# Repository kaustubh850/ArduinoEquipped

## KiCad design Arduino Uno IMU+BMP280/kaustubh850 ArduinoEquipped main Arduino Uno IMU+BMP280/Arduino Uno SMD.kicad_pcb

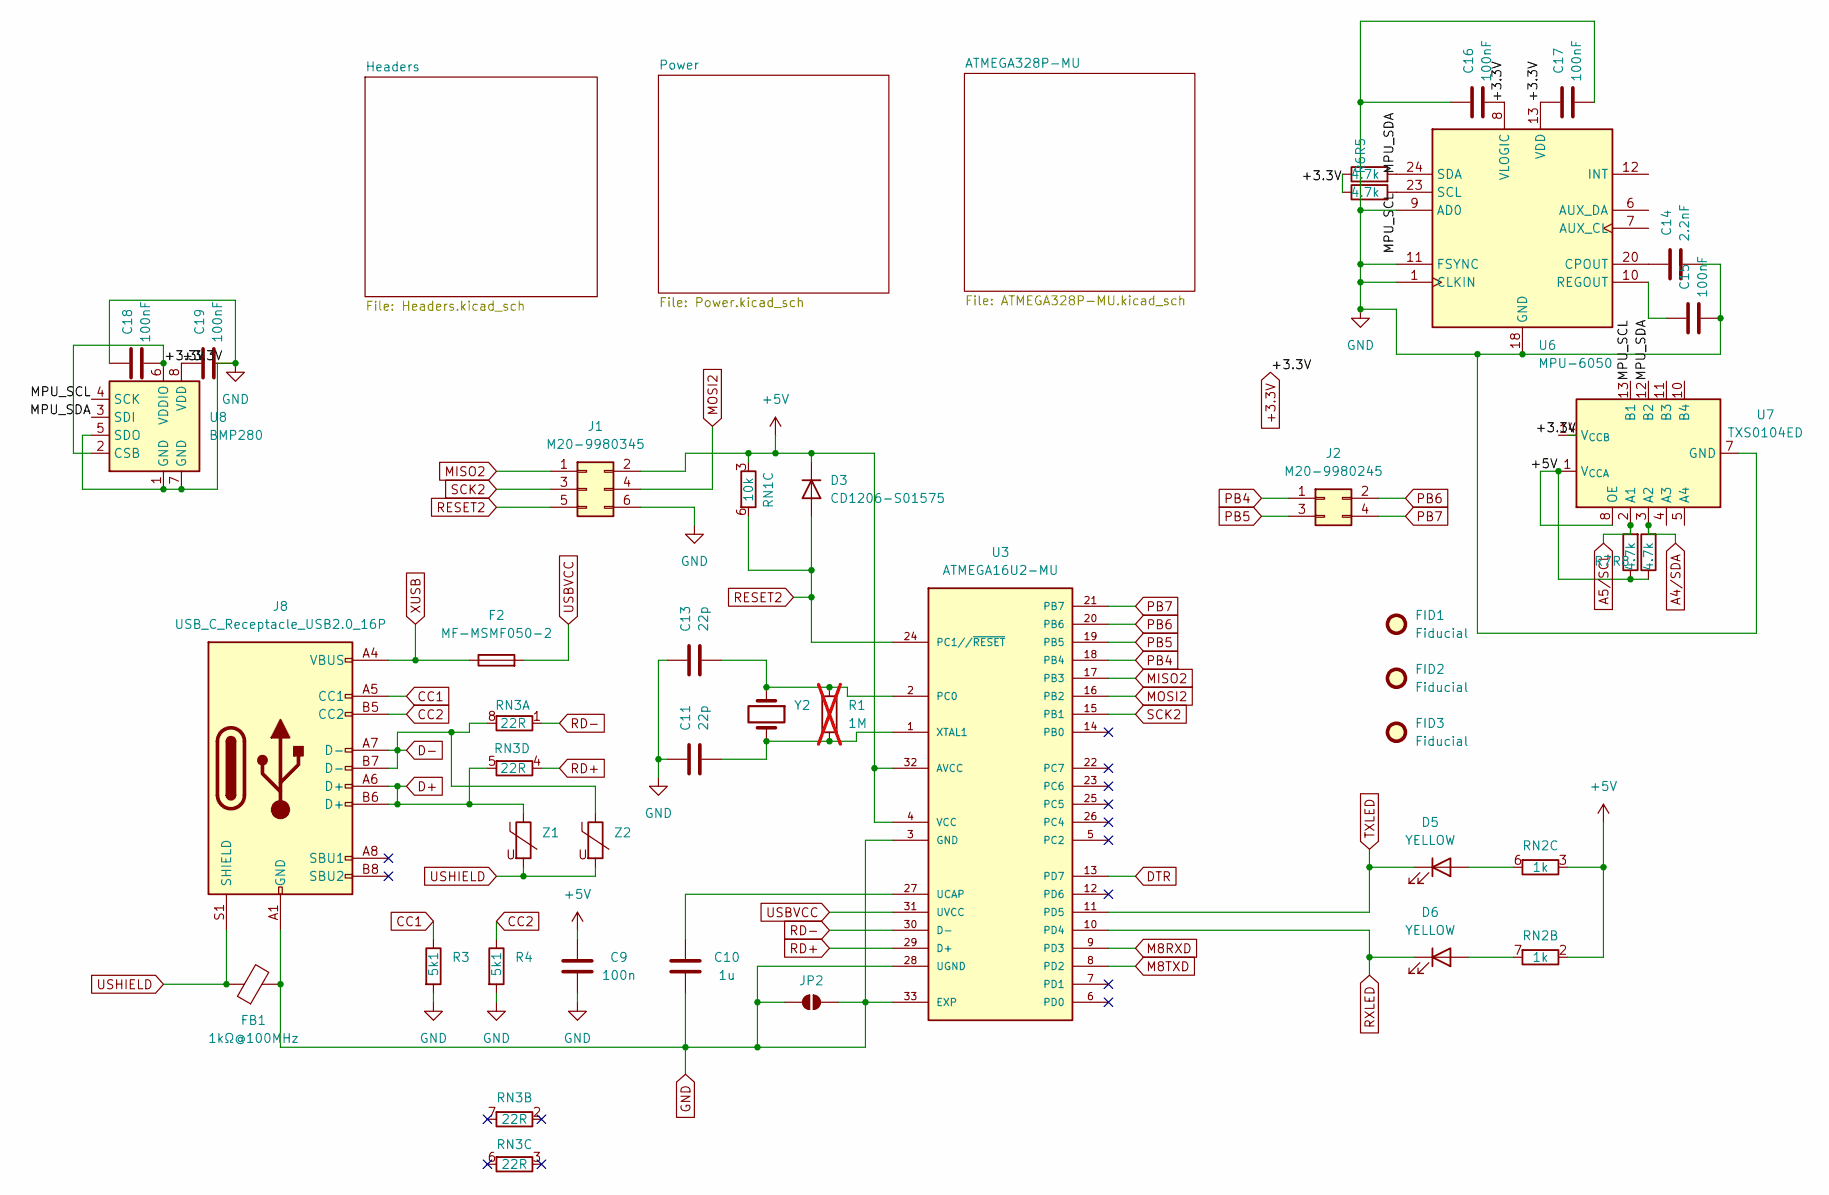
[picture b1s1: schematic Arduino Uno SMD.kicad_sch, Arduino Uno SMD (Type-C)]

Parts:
C9: 100n; C_0603_1608Metric
C10: 1u; C_0603_1608Metric
C11, C13: 22p; C_0603_1608Metric
C14: 2.2nF; C_0603_1608Metric
C15, C16, C17, C18, C19: 100nF; C_0603_1608Metric
D3: CD1206-S01575; D_1206_3216Metric
D5, D6: YELLOW; LED_0805_2012Metric
F2: MF-MSMF050-2; Fuse_1812_4532Metric_Pad1.30x3.40mm_HandSolder
FB1: 1kΩ@100MHz; L_0805_2012Metric
FID1, FID2, FID3: Fiducial; Fiducial_1mm_Mask2mm
J1: M20-9980345; PinHeader_2x03_P2.54mm_Vertical
J2: M20-9980245; CONN_M20-9980245_HRW
J8: USB_C_Receptacle_USB2.0_16P; USB_C_Receptacle_GCT_USB4105-xx-A_16P_TopMnt_Horizontal
JP2: SolderJumper_2_Open; SolderJumper-2_P1.3mm_Open_Pad1.0x1.5mm
R1: 1M; R_0603_1608Metric; not fitted
R3, R4: 5k1; R_0603_1608Metric
R5, R6, R7, R8: 4.7k; R_0603_1608Metric
RN1: 10k; R_Array_Convex_4x0603
RN2: 1k; R_Array_Convex_4x0603
RN3: 22R; R_Array_Convex_4x0603
U3: ATMEGA16U2-MU; VQFN-32-1EP_5x5mm_P0.5mm_EP3.1x3.1mm
U6: MPU-6050; InvenSense_QFN-24_4x4mm_P0.5mm
U7: TXS0104ED; SOIC-14_3.9x8.7mm_P1.27mm
U8: BMP280; Bosch_LGA-8_2x2.5mm_P0.65mm_ClockwisePinNumbering
Y2: LFXTAL003240BULK; Crystal_HC49-4H_Vertical
Z1, Z2: 5pF@1MHz; R_0603_1608Metric

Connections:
+3.3V: C16.1, C17.2, C18.1, C19.2, R5.1, R6.1, U6.8 (VLOGIC), U6.13 (VDD), U8.2 (CSB), U8.6 (VDDIO), U8.8 (VDD); also elsewhere on the board
+5V: C9.1, D3.1 (K), J1.2, R7.1, R8.1, RN1.3 (R3.1), RN2.2 (R2.1), RN2.3 (R3.1), U3.4 (VCC), U3.32 (AVCC), U7.1 (V_{CCA}), U7.8 (OE); also elsewhere on the board
/MPU_SCL: R6.2, U6.23 (SCL), U7.13 (B1), U8.4 (SCK)
/MPU_SDA: R5.2, U6.24 (SDA), U7.12 (B2), U8.3 (SDI)
A4/SDA: R8.2, U7.3 (A2); also elsewhere on the board
A5/SCL: R7.2, U7.2 (A1); also elsewhere on the board
CC1: J8.A5 (CC1), R3.1
CC2: J8.B5 (CC2), R4.1
D+: J8.A6 (D+), J8.B6 (D+), RN3.5 (R4.2), Z1.1
D-: J8.A7 (D-), J8.B7 (D-), RN3.8 (R1.2), Z2.1
DTR: U3.13 (PD7); also elsewhere on the board
GND: C9.2, C10.1, C11.2, C13.2, C14.1, C15.1, C16.2, C17.1, C18.2, C19.1, FB1.2, J1.6, J8.A1 (GND), J8.A12 (GND), J8.B1 (GND), J8.B12 (GND), JP2.1 (A), JP2.2 (B), R3.2, R4.2, U3.3 (GND), U3.28 (UGND), U3.33 (EXP), U6.1 (CLKIN), U6.9 (AD0), U6.11 (FSYNC), U6.18 (GND), U7.7 (GND), U8.1 (GND), U8.5 (SDO), U8.7 (GND); also elsewhere on the board
M8RXD: U3.9 (PD3); also elsewhere on the board
M8TXD: U3.8 (PD2); also elsewhere on the board
MISO2: J1.1, U3.17 (PB3)
MOSI2: J1.4, U3.16 (PB2)
unnamed: D5.2 (A), RN2.6 (R3.2)
unnamed: D6.2 (A), RN2.7 (R2.2)
unnamed: C13.1, R1.1, U3.2 (PC0), Y2.1
unnamed: C10.2, U3.27 (UCAP)
unnamed: C11.1, R1.2, U3.1 (XTAL1), Y2.2
unnamed: C14.2, U6.20 (CPOUT)
unnamed: C15.2, U6.10 (REGOUT)
PB4: J2.1, U3.18 (PB4)
PB5: J2.3, U3.19 (PB5)
PB6: J2.2, U3.20 (PB6)
PB7: J2.4, U3.21 (PB7)
RD+: RN3.4 (R4.1), U3.29 (D+)
RD-: RN3.1 (R1.1), U3.30 (D-)
RESET2: D3.2 (A), J1.5, RN1.6 (R3.2), U3.24 (PC1//~RESET)
RXLED: D6.1 (K), U3.10 (PD4)
SCK2: J1.3, U3.15 (PB1)
TXLED: D5.1 (K), U3.11 (PD5)
USBVCC: F2.2, U3.31 (UVCC); also elsewhere on the board
USHIELD: FB1.1, J8.S1 (SHIELD), Z1.2, Z2.2
XUSB: F2.1, J8.A4 (VBUS), J8.A9 (VBUS), J8.B4 (VBUS), J8.B9 (VBUS)

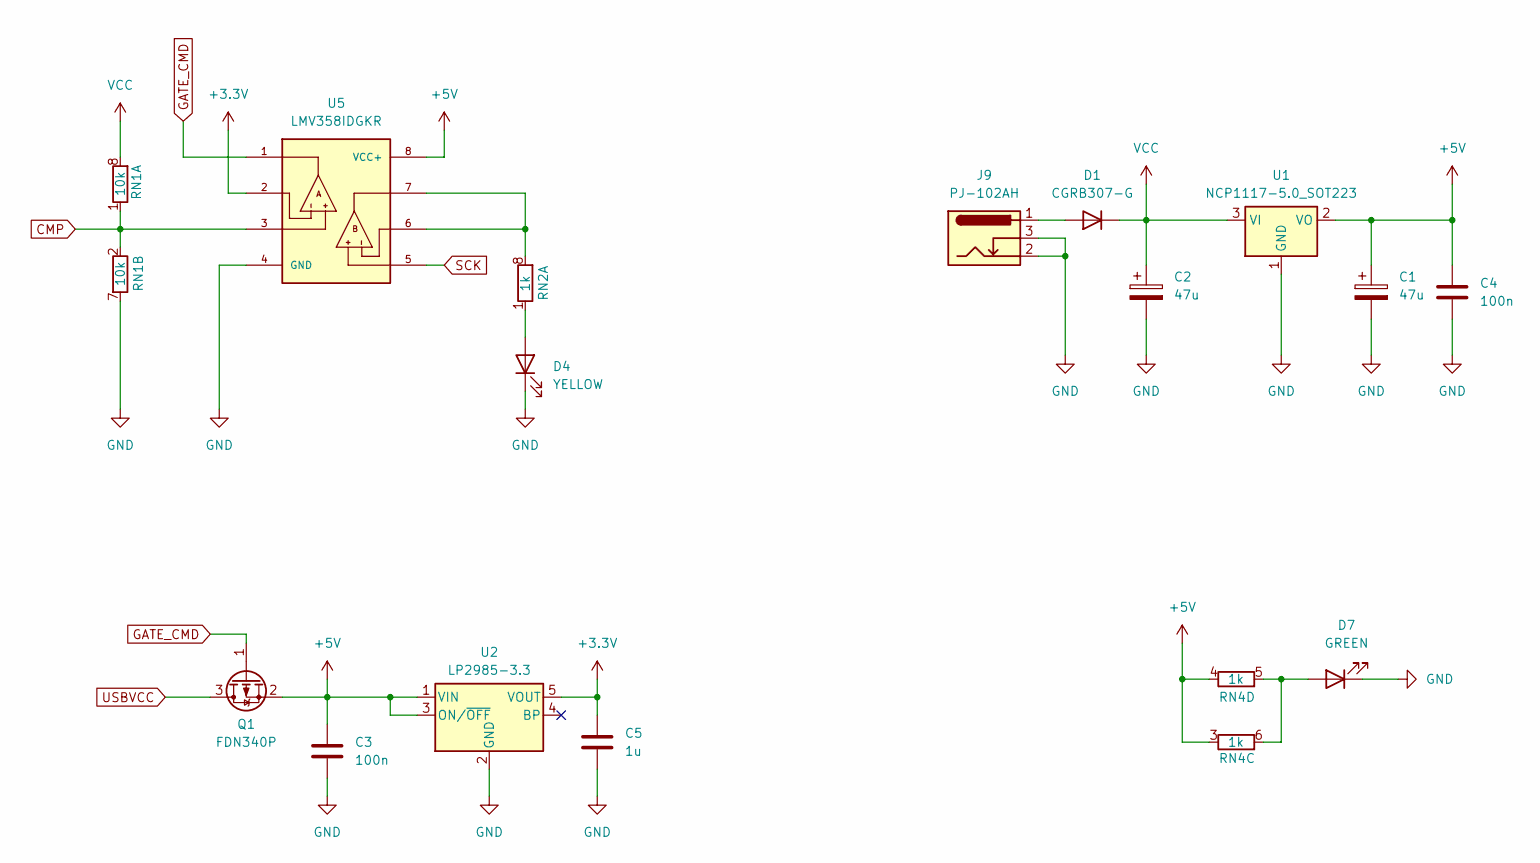
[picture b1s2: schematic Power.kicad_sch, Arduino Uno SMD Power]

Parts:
C1, C2: 47u; CAP_EEHZA1E470P
C3, C4: 100n; C_0603_1608Metric
C5: 1u; C_0603_1608Metric
D1: CGRB307-G; D_SMB
D4: YELLOW; LED_0805_2012Metric
D7: GREEN; LED_0805_2012Metric
J9: PJ-102AH; BarrelJack_Kycon_KLDX-0202-xC_Horizontal
Q1: FDN340P; SC-59
RN1: 10k; R_Array_Convex_4x0603
RN2, RN4: 1k; R_Array_Convex_4x0603
U1: NCP1117-5.0_SOT223; SOT-223-3_TabPin2
U2: LP2985-3.3; SOT-23-5
U5: LMV358IDGKR; MSOP-8_3x3mm_P0.65mm; PARTREV X

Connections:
+3.3V: C5.2, U2.5 (VOUT), U5.2; also elsewhere on the board
+5V: C1.1, C3.2, C4.1, Q1.2 (S), RN4.3 (R3.1), RN4.4 (R4.1), U1.2 (VO), U2.1 (VIN), U2.3 (ON/~OFF), U5.8 (VCC+); also elsewhere on the board
CMP: RN1.1 (R1.1), RN1.2 (R2.1), U5.3
GATE_CMD: Q1.1 (G), U5.1
GND: C1.2, C2.2, C3.1, C4.2, C5.1, D4.1 (K), D7.1 (K), J9.2, J9.3, RN1.7 (R2.2), U1.1 (GND), U2.2 (GND), U5.4 (GND); also elsewhere on the board
unnamed: D1.2 (A), J9.1
unnamed: D4.2 (A), RN2.1 (R1.1)
unnamed: D7.2 (A), RN4.5 (R4.2), RN4.6 (R3.2)
unnamed: RN2.8 (R1.2), U5.6, U5.7
SCK: U5.5; also elsewhere on the board
USBVCC: Q1.3 (D); also elsewhere on the board
VCC: C2.1, D1.1 (K), RN1.8 (R1.2), U1.3 (VI); also elsewhere on the board

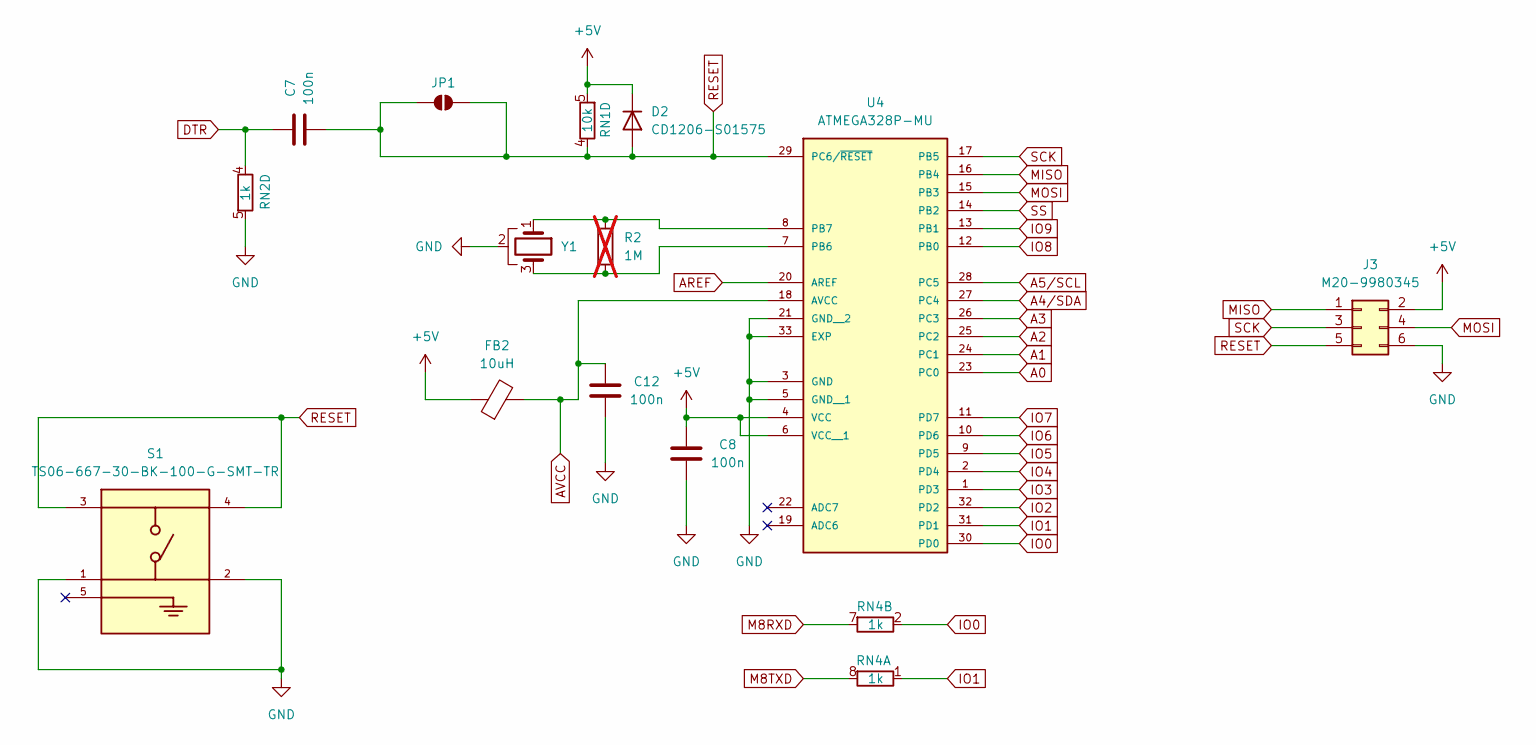
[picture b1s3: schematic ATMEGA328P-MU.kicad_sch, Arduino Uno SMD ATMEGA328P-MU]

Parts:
C7, C8, C12: 100n; C_0603_1608Metric
D2: CD1206-S01575; D_1206_3216Metric
FB2: 10uH; L_0805_2012Metric
J3: M20-9980345; PinHeader_2x03_P2.54mm_Vertical
JP1: SolderJumper_2_Open; SolderJumper-2_P1.3mm_Open_Pad1.0x1.5mm
R2: 1M; R_0603_1608Metric; not fitted
RN1: 10k; R_Array_Convex_4x0603
RN2, RN4: 1k; R_Array_Convex_4x0603
S1: TS06-667-30-BK-100-G-SMT-TR; SW_TS06-667-30-BK-100-G-SMT-TR; PARTREV 1.0
U4: ATMEGA328P-MU; VQFN-32-1EP_5x5mm_P0.5mm_EP3.1x3.1mm
Y1: CSTNE16M0V530000R0; Resonator_SMD_Murata_CSTxExxV-3Pin_3.0x1.1mm

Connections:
+5V: C8.2, D2.1 (K), FB2.1, J3.2, RN1.5 (R4.2), U4.4 (VCC), U4.6 (VCC__1); also elsewhere on the board
A0: U4.23 (PC0); also elsewhere on the board
A1: U4.24 (PC1); also elsewhere on the board
A2: U4.25 (PC2); also elsewhere on the board
A3: U4.26 (PC3); also elsewhere on the board
A4/SDA: U4.27 (PC4); also elsewhere on the board
A5/SCL: U4.28 (PC5); also elsewhere on the board
AREF: U4.20 (AREF); also elsewhere on the board
AVCC: C12.1, FB2.2, U4.18 (AVCC)
DTR: C7.1, RN2.4 (R4.1); also elsewhere on the board
GND: C8.1, C12.2, J3.6, RN2.5 (R4.2), S1.1, S1.2, U4.3 (GND), U4.5 (GND__1), U4.21 (GND__2), U4.33 (EXP), Y1.2; also elsewhere on the board
IO0: RN4.2 (R2.1), U4.30 (PD0); also elsewhere on the board
IO1: RN4.1 (R1.1), U4.31 (PD1); also elsewhere on the board
IO2: U4.32 (PD2); also elsewhere on the board
IO3: U4.1 (PD3); also elsewhere on the board
IO4: U4.2 (PD4); also elsewhere on the board
IO5: U4.9 (PD5); also elsewhere on the board
IO6: U4.10 (PD6); also elsewhere on the board
IO7: U4.11 (PD7); also elsewhere on the board
IO8: U4.12 (PB0); also elsewhere on the board
IO9: U4.13 (PB1); also elsewhere on the board
M8RXD: RN4.7 (R2.2); also elsewhere on the board
M8TXD: RN4.8 (R1.2); also elsewhere on the board
MISO: J3.1, U4.16 (PB4); also elsewhere on the board
MOSI: J3.4, U4.15 (PB3); also elsewhere on the board
unnamed: R2.2, U4.7 (PB6), Y1.3
unnamed: R2.1, U4.8 (PB7), Y1.1
RESET: C7.2, D2.2 (A), J3.5, JP1.1 (A), JP1.2 (B), RN1.4 (R4.1), S1.3, S1.4, U4.29 (PC6/~RESET); also elsewhere on the board
SCK: J3.3, U4.17 (PB5); also elsewhere on the board
SS: U4.14 (PB2); also elsewhere on the board

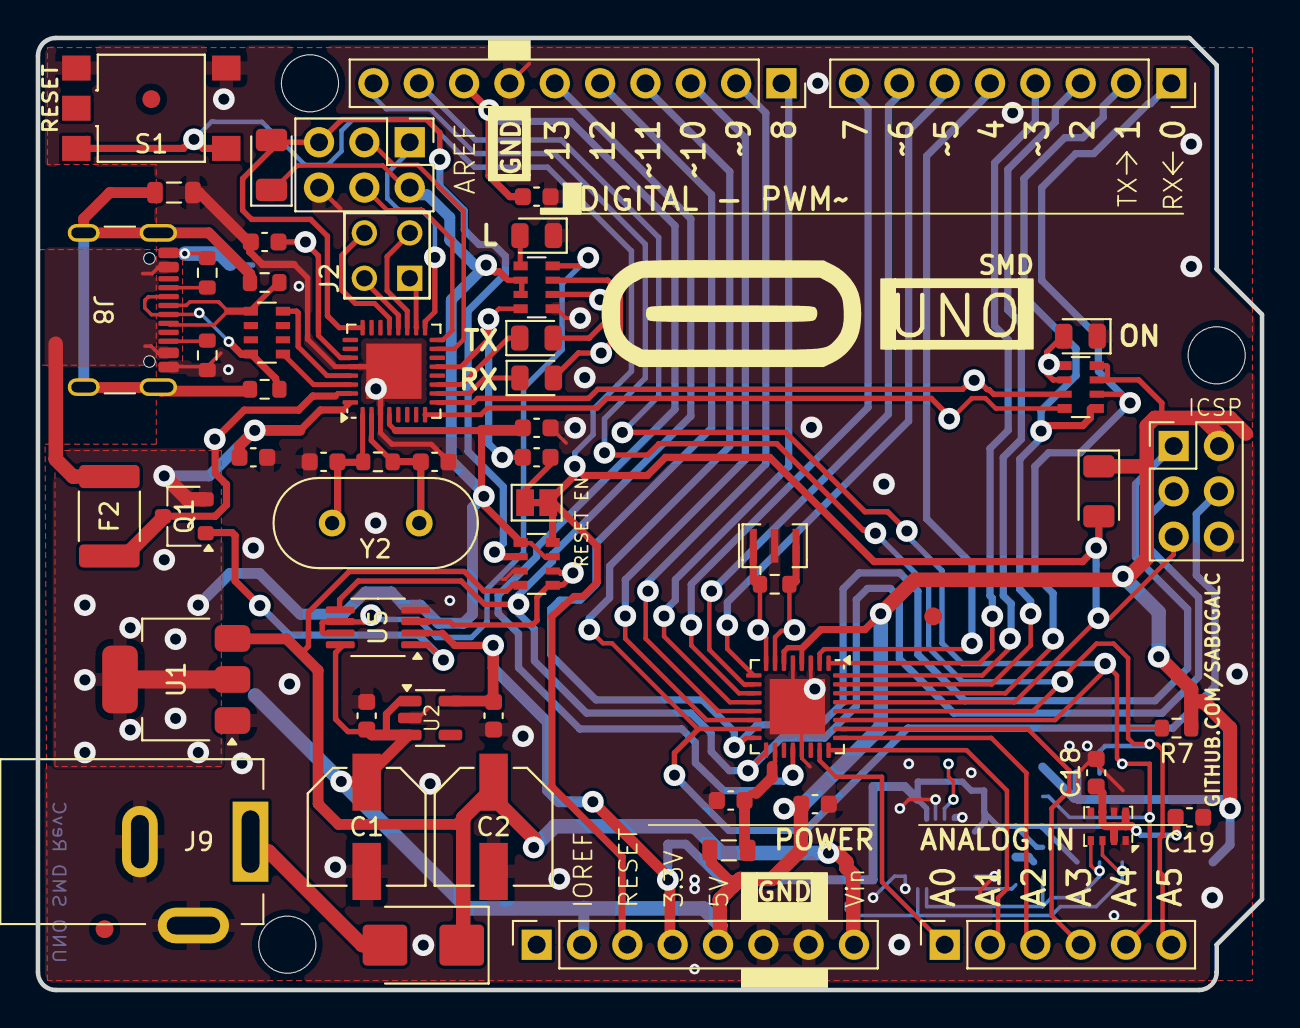
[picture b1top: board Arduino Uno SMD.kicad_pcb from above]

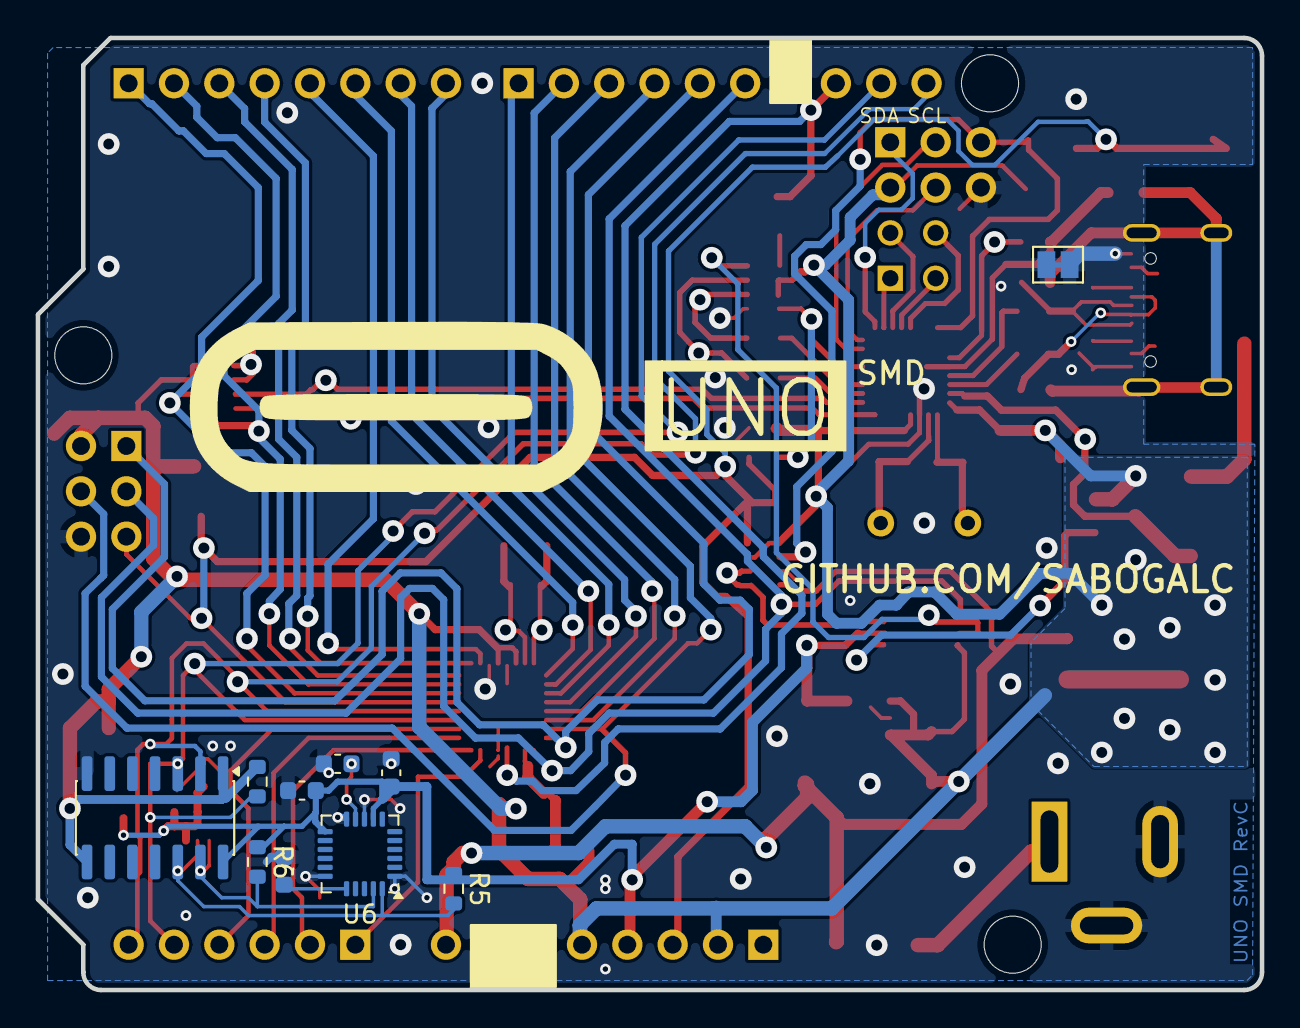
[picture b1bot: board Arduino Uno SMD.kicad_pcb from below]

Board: 2 copper layers, 68.6 x 53.3 mm, 69 parts (10 on the bottom side), 66 nets.

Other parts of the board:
C6: 100n; C_0603_1608Metric
J4: PPTC101LFBN-RC; PinSocket_1x10_P2.54mm_Vertical
J5, J7: PPTC081LFBN-RC; PinSocket_1x08_P2.54mm_Vertical
J6: PPTC061LFBN-RC; PinSocket_1x06_P2.54mm_Vertical

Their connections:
+3.3V: J7.4; also elsewhere on the board
+5V: J7.2, J7.5; also elsewhere on the board
A0: J6.1; also elsewhere on the board
A1: J6.2; also elsewhere on the board
A2: J6.3; also elsewhere on the board
A3: J6.4; also elsewhere on the board
A4/SDA: J4.9, J6.5; also elsewhere on the board
A5/SCL: J4.10, J6.6; also elsewhere on the board
AREF: C6.1, J4.8; also elsewhere on the board
GND: C6.2, J4.7, J7.6, J7.7; also elsewhere on the board
IO0: J5.1; also elsewhere on the board
IO1: J5.2; also elsewhere on the board
IO2: J5.3; also elsewhere on the board
IO3: J5.4; also elsewhere on the board
IO4: J5.5; also elsewhere on the board
IO5: J5.6; also elsewhere on the board
IO6: J5.7; also elsewhere on the board
IO7: J5.8; also elsewhere on the board
IO8: J4.1; also elsewhere on the board
IO9: J4.2; also elsewhere on the board
MISO: J4.5; also elsewhere on the board
MOSI: J4.4; also elsewhere on the board
RESET: J7.3; also elsewhere on the board
SCK: J4.6; also elsewhere on the board
SS: J4.3; also elsewhere on the board
VCC: J7.8; also elsewhere on the board

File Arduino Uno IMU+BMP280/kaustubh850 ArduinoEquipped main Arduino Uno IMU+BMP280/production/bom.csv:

Designator,Footprint,Quantity,Value,LCSC Part #
"C1, C2",CAP_EEHZA1E470P,2,47u,
"C10, C5",0603,2,1u,
"C11, C13",0603,2,22p,
"C12, C3, C4, C6, C7, C8, C9",0603,7,100n,
C14,0603,1,2.2nF,
"C15, C16, C17, C18, C19",0603,5,100nF,
D1,D_SMB,1,CGRB307-G,
"D2, D3",1206,2,CD1206-S01575,
"D4, D5, D6",0805,3,YELLOW,
D7,0805,1,GREEN,
F2,1812,1,MF-MSMF050-2,
FB1,0805,1,1kΩ@100MHz,
FB2,0805,1,10uH,
"J1, J3",PinHeader_2x03_P2.54mm_Vertical,2,M20-9980345,
J2,CONN_M20-9980245_HRW,1,M20-9980245,
J4,PinSocket_1x10_P2.54mm_Vertical,1,PPTC101LFBN-RC,
"J5, J7",PinSocket_1x08_P2.54mm_Vertical,2,PPTC081LFBN-RC,
J6,PinSocket_1x06_P2.54mm_Vertical,1,PPTC061LFBN-RC,
J8,USB_C_Receptacle_GCT_USB4105-xx-A_16P_TopMnt_Horizontal,1,USB_C_Receptacle_USB2.0_16P,
J9,BarrelJack_Kycon_KLDX-0202-xC_Horizontal,1,PJ-102AH,
Q1,SC-59,1,FDN340P,
"R3, R4",0603,2,5k1,
"R5, R6, R7, R8",0603,4,4.7k,
RN1,R_Array_Convex_4x0603,1,10k,
"RN2, RN4",R_Array_Convex_4x0603,2,1k,
RN3,R_Array_Convex_4x0603,1,22R,
S1,SW_TS06-667-30-BK-100-G-SMT-TR,1,TS06-667-30-BK-100-G-SMT-TR,
U1,SOT-223-3_TabPin2,1,NCP1117-5.0_SOT223,
U2,SOT-23-5,1,LP2985-3.3,
U3,VQFN-32-1EP_5x5mm_P0.5mm_EP3.1x3.1mm,1,ATMEGA16U2-MU,
U4,VQFN-32-1EP_5x5mm_P0.5mm_EP3.1x3.1mm,1,ATMEGA328P-MU,
U5,MSOP-8_3x3mm_P0.65mm,1,LMV358IDGKR,
U6,InvenSense_QFN-24_4x4mm_P0.5mm,1,MPU-6050,
U7,SOIC-14_3.9x8.7mm_P1.27mm,1,ET2104V,
U8,Bosch_LGA-8_2x2.5mm_P0.65mm_ClockwisePinNumbering,1,BMP280,
Y1,Resonator_SMD_Murata_CSTxExxV-3Pin_3.0x1.1mm,1,CSTNE16M0V530000R0,
Y2,Crystal_HC49-4H_Vertical,1,LFXTAL003240BULK,
"Z1, Z2",0603,2,5pF@1MHz,
